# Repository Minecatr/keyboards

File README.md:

# Compiling firmware with QMK MSYS
- Install [QMK MSYS](https://msys.qmk.fm/)
- Setup QMK MSYS
- Clone this project into `qmk_firmware/keyboards/minecatr` *this means this repositories contents go in here
- Copy the build folder of the desired keyboard into the QMK MSYS directory
- Run `qmk compile -e CONVERT_TO=promicro_rp2040 -kb {PATH TO KEYBOARD} -km default` in QMK MSYS
- Output should be in `qmk_firmware/.build`
## Using other bootloaders
If your MCU does not use UF2 it likely supports one of these other bootloaders
### Caterina
`qmk flash -kb /build -km default`

### [Other Bootloaders](https://github.com/qmk/qmk_firmware/blob/master/docs/flashing.md)
# Using VIA to change layout
- Install [VIA](https://github.com/the-via/releases/releases) or use the [web version](https://www.usevia.app/)
- Navigate to settings and enable show design tab
- Navigate to design and press load
- Select the the via.json file of the desired board

a preconfigured layout.json is in each complete board

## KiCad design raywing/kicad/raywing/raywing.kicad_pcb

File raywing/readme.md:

# RAYWING

a split choc keyboard with 54 backlit keys 2 rotary encoders and a flippable board
## Parts
- RGB LEDs: SK6812 MINI-E 100pcs https://www.aliexpress.us/item/2255800289371100.html
- MCU: Any Arduino Pro Micro Form Board
- EVQWGD001 Encoder: https://www.aliexpress.us/item/3256806010310254.html
- Diodes: DO-35 1N4148 100pcs https://www.aliexpress.us/item/3256805608834808.html
- Hotswap: Mill-Max Sockets (any) https://ringerkeys.com/collections/modders-tools/products/mill-max-hot-swap-sockets?variant=32793029312594](https://mech.land/products/mill-max-sockets?variant=39832065081497
- Switches: Any Choc V1 Compatible https://chosfox.com/collections/kailh-low-profile-switch-pg1350/products/kailh-chocs
- Keycaps: Any Choc V1 Compatible
- TRRS: PJ-320A https://www.aliexpress.us/item/2251832843150354.html
- TRRS Cable: Any 4 Ring TRRS Cable
  - If you have a 3 ring cut off the last pin on the TRRS socket
## Ordering A PCB
1. Download Gerbers Located `/kicad/production/Raywing.zip`
2. Choose Preferred PCB service
  - JLCPCB: https://cart.jlcpcb.com/quote
  - PCBWAY: https://www.pcbway.com/
  - DIGIKEY: https://www.digikey.com/en/resources/design-tools/pcb-build
3. Upload Gerbers
4. Order PCB

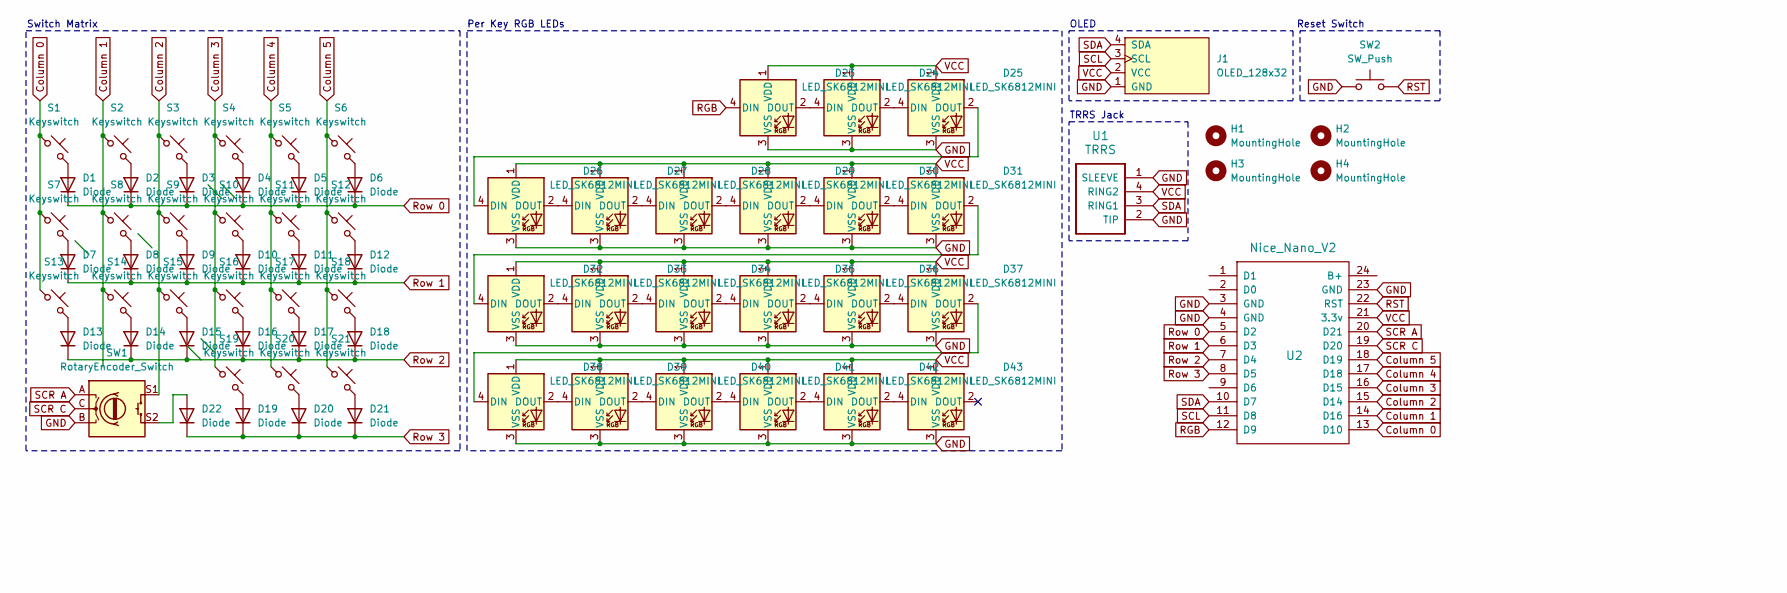
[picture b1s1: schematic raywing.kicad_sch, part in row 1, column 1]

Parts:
D1, D2, D3, D4, D5, D6, D7, D8, D9, D10, D11, D12, D13, D14, D15, D16, D17, D18, D19, D20, D21, D22: Diode; Diode_DO-35-FLIP
D23, D24, D25, D26, D27, D28, D29, D30, D31, D32, D33, D34, D35, D36, D37, D38, D39, D40, D41, D42, D43: LED_SK6812MINI; SK6812_mini_e_flipable
H1, H2, H3, H4: MountingHole; MountingHole_2.2mm_M2_Pad_Via
J1: OLED_128x32
S1, S2, S3, S4, S5, S6, S7, S8, S9, S10, S11, S12, S13, S14, S15, S16, S17, S18, S19, S20, S21: Keyswitch; Hotswap_Choc_FLIP
SW1: RotaryEncoder_Switch; evqwgd001
SW2: SW_Push; SW_SPST_TL3342_FLIP
U1: TRRS; TRRS_PJ-320A_FLIP
U2: Nice_Nano_V2

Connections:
Column 0: S1.1, S7.1, S13.1, U2.13 (D10)
Column 1: S2.1, S8.1, S14.1, U2.14 (D16)
Column 2: S3.1, S9.1, S15.1, SW1.S1, U2.15 (D14)
Column 3: S4.1, S10.1, S16.1, S19.1, U2.16 (D15)
Column 4: S5.1, S11.1, S17.1, S20.1, U2.17 (D18)
Column 5: S6.1, S12.1, S18.1, S21.1, U2.18 (D19)
GND: D23.3 (VSS), D24.3 (VSS), D25.3 (VSS), D26.3 (VSS), D27.3 (VSS), D28.3 (VSS), D29.3 (VSS), D30.3 (VSS), D31.3 (VSS), D32.3 (VSS), D33.3 (VSS), D34.3 (VSS), D35.3 (VSS), D36.3 (VSS), D37.3 (VSS), D38.3 (VSS), D39.3 (VSS), D40.3 (VSS), D41.3 (VSS), D42.3 (VSS), D43.3 (VSS), J1.1 (GND), SW1.B, SW2.1, U1.1 (SLEEVE), U1.2 (TIP), U2.3 (GND), U2.4 (GND), U2.23 (GND)
unnamed: D1.2 (A), S1.2
unnamed: D2.2 (A), S2.2
unnamed: D3.2 (A), S3.2
unnamed: D4.2 (A), S4.2
unnamed: D5.2 (A), S5.2
unnamed: D6.2 (A), S6.2
unnamed: D7.2 (A), S7.2
unnamed: D8.2 (A), S8.2
unnamed: D9.2 (A), S9.2
unnamed: D10.2 (A), S10.2
unnamed: D11.2 (A), S11.2
unnamed: D12.2 (A), S12.2
unnamed: D13.2 (A), S13.2
unnamed: D14.2 (A), S14.2
unnamed: D15.2 (A), S15.2
unnamed: D16.2 (A), S16.2
unnamed: D17.2 (A), S17.2
unnamed: D18.2 (A), S18.2
unnamed: D19.2 (A), S19.2
unnamed: D20.2 (A), S20.2
unnamed: D21.2 (A), S21.2
unnamed: D22.2 (A), SW1.S2
unnamed: D23.2 (DOUT), D24.4 (DIN)
unnamed: D24.2 (DOUT), D25.4 (DIN)
unnamed: D25.2 (DOUT), D26.4 (DIN)
unnamed: D26.2 (DOUT), D27.4 (DIN)
unnamed: D27.2 (DOUT), D28.4 (DIN)
unnamed: D28.2 (DOUT), D29.4 (DIN)
unnamed: D29.2 (DOUT), D30.4 (DIN)
unnamed: D30.2 (DOUT), D31.4 (DIN)
unnamed: D31.2 (DOUT), D32.4 (DIN)
unnamed: D32.2 (DOUT), D33.4 (DIN)
unnamed: D33.2 (DOUT), D34.4 (DIN)
unnamed: D34.2 (DOUT), D35.4 (DIN)
unnamed: D35.2 (DOUT), D36.4 (DIN)
unnamed: D36.2 (DOUT), D37.4 (DIN)
unnamed: D37.2 (DOUT), D38.4 (DIN)
unnamed: D38.2 (DOUT), D39.4 (DIN)
unnamed: D39.2 (DOUT), D40.4 (DIN)
unnamed: D40.2 (DOUT), D41.4 (DIN)
unnamed: D41.2 (DOUT), D42.4 (DIN)
unnamed: D42.2 (DOUT), D43.4 (DIN)
RGB: D23.4 (DIN), U2.12 (D9)
RST: SW2.2, U2.22 (RST)
Row 0: D1.1 (K), D2.1 (K), D3.1 (K), D4.1 (K), D5.1 (K), D6.1 (K), U2.5 (D2)
Row 1: D7.1 (K), D8.1 (K), D9.1 (K), D10.1 (K), D11.1 (K), D12.1 (K), U2.6 (D3)
Row 2: D13.1 (K), D14.1 (K), D15.1 (K), D16.1 (K), D17.1 (K), D18.1 (K), U2.7 (D4)
Row 3: D19.1 (K), D20.1 (K), D21.1 (K), D22.1 (K), U2.8 (D5)
SCL: J1.3 (SCL), U2.11 (D8)
SCR A: SW1.A, U2.20 (D21)
SCR C: SW1.C, U2.19 (D20)
SDA: J1.4 (SDA), U1.3 (RING1), U2.10 (D7)
VCC: D23.1 (VDD), D24.1 (VDD), D25.1 (VDD), D26.1 (VDD), D27.1 (VDD), D28.1 (VDD), D29.1 (VDD), D30.1 (VDD), D31.1 (VDD), D32.1 (VDD), D33.1 (VDD), D34.1 (VDD), D35.1 (VDD), D36.1 (VDD), D37.1 (VDD), D38.1 (VDD), D39.1 (VDD), D40.1 (VDD), D41.1 (VDD), D42.1 (VDD), D43.1 (VDD), J1.2 (VCC), U1.4 (RING2), U2.21 (3.3v)

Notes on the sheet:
Switch Matrix
Reset Switch
OLED
TRRS Jack
Per Key RGB LEDs

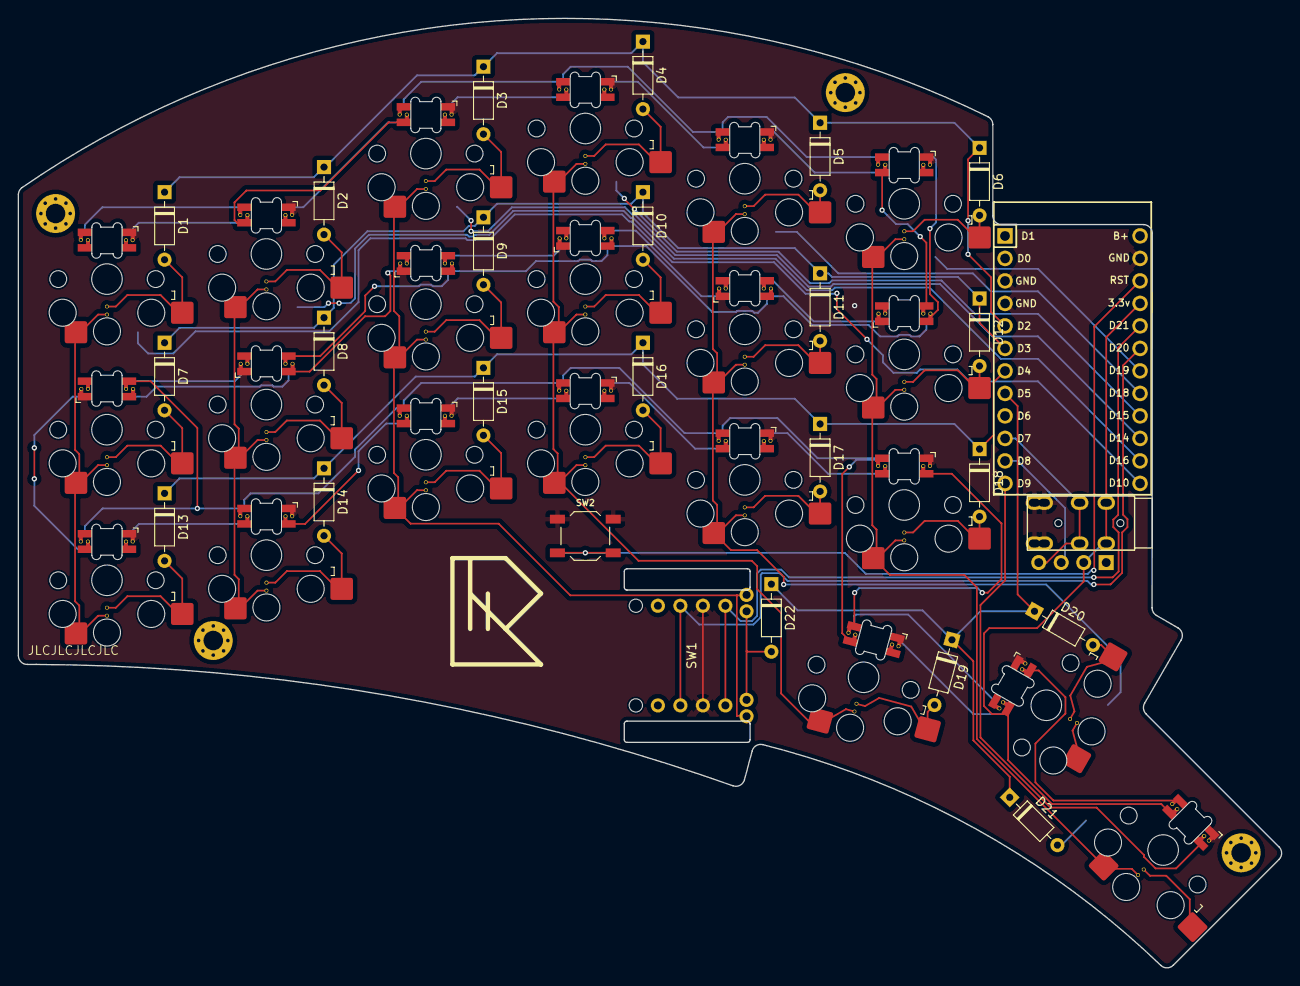
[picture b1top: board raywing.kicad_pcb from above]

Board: 2 copper layers, 142.6 x 107.2 mm, 73 parts (0 on the bottom side), 60 nets.

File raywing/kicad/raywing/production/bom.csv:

Designator,Footprint,Quantity,Value,LCSC Part #
"D1, D10, D11, D12, D13, D14, D15, D16, D17, D18, D19, D2, D20, D21, D22, D3, D4, D5, D6, D7, D8, D9",Diode_DO-35-FLIP,22,Diode,
"D23, D24, D25, D26, D27, D28, D29, D30, D31, D32, D33, D34, D35, D36, D37, D38, D39, D40, D41, D42, D43",SK6812_mini_e_flipable,21,LED_SK6812MINI,
J1,OLED_128x32,1,OLED_128x32,
"S1, S10, S11, S12, S13, S14, S15, S16, S17, S18, S19, S2, S20, S21, S3, S4, S5, S6, S7, S8, S9",Hotswap_Choc_FLIP,21,Keyswitch,
SW1,evqwgd001,1,RotaryEncoder_Switch,
SW2,SW_SPST_TL3342_FLIP,1,SW_Push,
U1,TRRS_PJ-320A_FLIP,1,TRRS,
U2,Nice_Nano_V2,1,Nice_Nano_V2,

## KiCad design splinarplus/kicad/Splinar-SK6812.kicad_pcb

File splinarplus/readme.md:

# Splinar+

(keys are scratched in btw; mbk keycaps expensive)

a split choc keyboard with 54 backlit keys 2 rotary encoders and a flippable board
## Parts
- RGB LEDs: SK6812 MINI-E 100pcs https://www.aliexpress.us/item/2255800289371100.html
- MCU: Any Arduino Pro Micro Form Board
- EVQWGD001 Encoder: https://www.aliexpress.us/item/3256806010310254.html
- Diodes: DO-35 1N4148 100pcs https://www.aliexpress.us/item/3256805608834808.html
- Hotswap: Mill-Max Sockets (any) https://ringerkeys.com/collections/modders-tools/products/mill-max-hot-swap-sockets?variant=32793029312594](https://mech.land/products/mill-max-sockets?variant=39832065081497
- Switches: Any Choc V1 Compatible https://chosfox.com/collections/kailh-low-profile-switch-pg1350/products/kailh-chocs
- Keycaps: Any Choc V1 Compatible
- TRRS: PJ-320A https://www.aliexpress.us/item/2251832843150354.html
- TRRS Cable: Any 4 Ring TRRS Cable
  - If you have a 3 ring cut off the last pin on the TRRS socket
## Ordering A PCB
1. Download Gerbers Located `/kicad/production/Splinar.zip`
2. Choose Preferred PCB service
  - JLCPCB: https://cart.jlcpcb.com/quote
  - PCBWAY: https://www.pcbway.com/
  - DIGIKEY: https://www.digikey.com/en/resources/design-tools/pcb-builde
3. Upload Gerbers
4. Order PCB

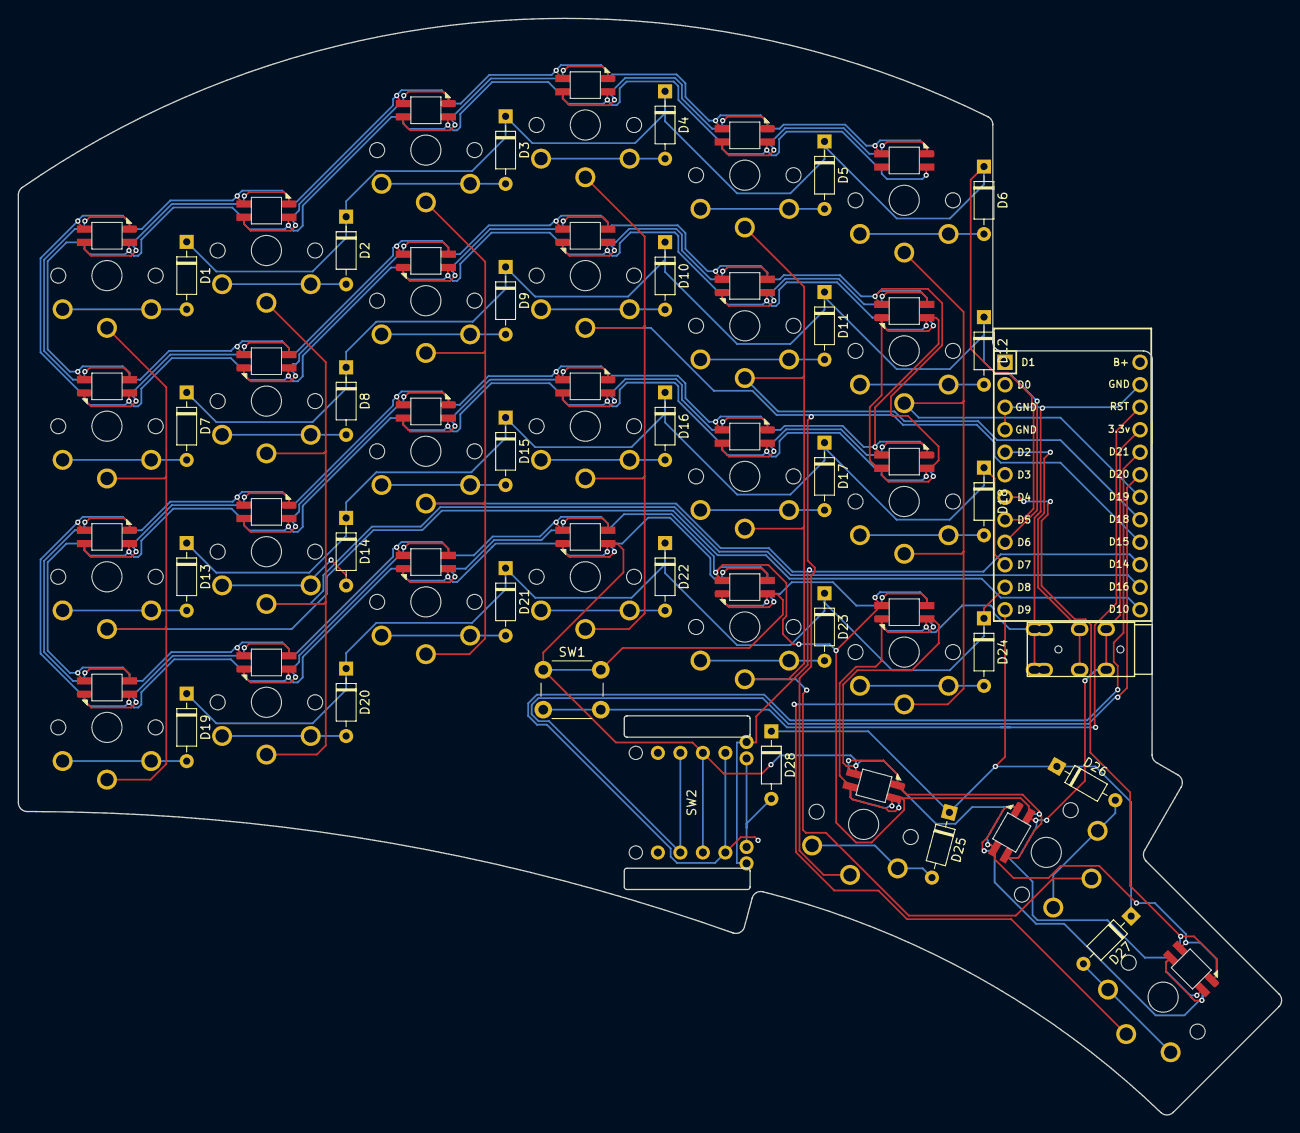
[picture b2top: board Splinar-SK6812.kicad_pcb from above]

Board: 2 copper layers, 142.6 x 123.8 mm, 86 parts (0 on the bottom side), 72 nets.

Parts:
D1, D2, D3, D4, D5, D6, D7, D8, D9, D10, D11, D12, D13, D14, D15, D16, D17, D18, D19, D20, D21, D22, D23, D24, D25, D26, D27, D28: Diode; Diode_DO-35-FLIP
D29, D30, D31, D32, D33, D34, D35, D36, D37, D38, D39, D40, D41, D42, D43, D44, D45, D46, D47, D48, D49, D50, D51, D52, D53, D54, D55: LED_SK6812MINI
S1, S2, S3, S4, S5, S6, S7, S8, S9, S10, S11, S12, S13, S14, S15, S16, S17, S18, S19, S20, S21, S22, S23, S24, S25, S26, S27: Keyswitch; Kailh-PG1350-1u-reversible-No-Clickhole
SW1: SW_Push; SW_PUSH_6mm_H4.3mm
SW2: RotaryEncoder_Switch; evqwgd001
U1: TRRS; TRRS_PJ-320A_FLIP
U2: Nice_Nano_V2

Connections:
Column 0: S1.1, S7.1, S13.1, S19.1, U2.13 (D10)
Column 1: S2.1, S8.1, S14.1, S20.1, U2.14 (D16)
Column 2: S3.1, S9.1, S15.1, S21.1, SW2.S1, U2.15 (D14)
Column 3: S4.1, S10.1, S16.1, S22.1, S25.1, U2.16 (D15)
Column 4: S5.1, S11.1, S17.1, S23.1, S26.1, U2.17 (D18)
Column 5: S6.1, S12.1, S18.1, S24.1, S27.1, U2.18 (D19)
GND: D29.2 (VSS), D30.2 (VSS), D31.2 (VSS), D32.2 (VSS), D33.2 (VSS), D34.2 (VSS), D35.2 (VSS), D36.2 (VSS), D37.2 (VSS), D38.2 (VSS), D39.2 (VSS), D40.2 (VSS), D41.2 (VSS), D42.2 (VSS), D43.2 (VSS), D44.2 (VSS), D45.2 (VSS), D46.2 (VSS), D47.2 (VSS), D48.2 (VSS), D49.2 (VSS), D50.2 (VSS), D51.2 (VSS), D52.2 (VSS), D53.2 (VSS), D54.2 (VSS), D55.2 (VSS), SW1.1, SW2.B, U1.1 (SLEEVE), U1.2 (TIP), U2.3 (GND), U2.4 (GND), U2.23 (GND)
unnamed: D1.2 (A), S1.2
unnamed: D2.2 (A), S2.2
unnamed: D3.2 (A), S3.2
unnamed: D4.2 (A), S4.2
unnamed: D5.2 (A), S5.2
unnamed: D6.2 (A), S6.2
unnamed: D7.2 (A), S7.2
unnamed: D8.2 (A), S8.2
unnamed: D9.2 (A), S9.2
unnamed: D10.2 (A), S10.2
unnamed: D11.2 (A), S11.2
unnamed: D12.2 (A), S12.2
unnamed: D13.2 (A), S13.2
unnamed: D14.2 (A), S14.2
unnamed: D15.2 (A), S15.2
unnamed: D16.2 (A), S16.2
unnamed: D17.2 (A), S17.2
unnamed: D18.2 (A), S18.2
unnamed: D19.2 (A), S19.2
unnamed: D20.2 (A), S20.2
unnamed: D21.2 (A), S21.2
unnamed: D22.2 (A), S22.2
unnamed: D23.2 (A), S23.2
unnamed: D24.2 (A), S24.2
unnamed: D25.2 (A), S25.2
unnamed: D26.2 (A), S26.2
unnamed: D27.2 (A), S27.2
unnamed: D28.2 (A), SW2.S2
unnamed: D29.3 (DIN), D55.1 (DOUT)
unnamed: D30.1 (DOUT), D31.3 (DIN)
unnamed: D31.1 (DOUT), D32.3 (DIN)
unnamed: D32.1 (DOUT), D33.3 (DIN)
unnamed: D33.1 (DOUT), D34.3 (DIN)
unnamed: D34.1 (DOUT), D35.3 (DIN)
unnamed: D35.1 (DOUT), D36.3 (DIN)
unnamed: D36.1 (DOUT), D37.3 (DIN)
unnamed: D37.1 (DOUT), D38.3 (DIN)
unnamed: D38.1 (DOUT), D39.3 (DIN)
unnamed: D39.1 (DOUT), D40.3 (DIN)
unnamed: D40.1 (DOUT), D41.3 (DIN)
unnamed: D41.1 (DOUT), D42.3 (DIN)
unnamed: D42.1 (DOUT), D43.3 (DIN)
unnamed: D43.1 (DOUT), D44.3 (DIN)
unnamed: D44.1 (DOUT), D45.3 (DIN)
unnamed: D45.1 (DOUT), D46.3 (DIN)
unnamed: D46.1 (DOUT), D47.3 (DIN)
unnamed: D47.1 (DOUT), D48.3 (DIN)
unnamed: D48.1 (DOUT), D49.3 (DIN)
unnamed: D49.1 (DOUT), D50.3 (DIN)
unnamed: D50.1 (DOUT), D51.3 (DIN)
unnamed: D51.1 (DOUT), D52.3 (DIN)
unnamed: D52.1 (DOUT), D53.3 (DIN)
unnamed: D53.1 (DOUT), D54.3 (DIN)
unnamed: D54.1 (DOUT), D55.3 (DIN)
RGB: D30.3 (DIN), U2.7 (D4)
RST: SW1.2, U2.22 (RST)
Row 0: D1.1 (K), D2.1 (K), D3.1 (K), D4.1 (K), D5.1 (K), D6.1 (K), U2.8 (D5)
Row 1: D7.1 (K), D8.1 (K), D9.1 (K), D10.1 (K), D11.1 (K), D12.1 (K), U2.9 (D6)
Row 2: D13.1 (K), D14.1 (K), D15.1 (K), D16.1 (K), D17.1 (K), D18.1 (K), U2.10 (D7)
Row 3: D19.1 (K), D20.1 (K), D21.1 (K), D22.1 (K), D23.1 (K), D24.1 (K), U2.11 (D8)
Row 4: D25.1 (K), D26.1 (K), D27.1 (K), D28.1 (K), U2.12 (D9)
SCR A: SW2.A, U2.20 (D21)
SCR C: SW2.C, U2.19 (D20)
SDA: U1.3 (RING1), U2.5 (D2)
VCC: D29.4 (VDD), D30.4 (VDD), D31.4 (VDD), D32.4 (VDD), D33.4 (VDD), D34.4 (VDD), D35.4 (VDD), D36.4 (VDD), D37.4 (VDD), D38.4 (VDD), D39.4 (VDD), D40.4 (VDD), D41.4 (VDD), D42.4 (VDD), D43.4 (VDD), D44.4 (VDD), D45.4 (VDD), D46.4 (VDD), D47.4 (VDD), D48.4 (VDD), D49.4 (VDD), D50.4 (VDD), D51.4 (VDD), D52.4 (VDD), D53.4 (VDD), D54.4 (VDD), D55.4 (VDD), U1.4 (RING2), U2.21 (3.3v)

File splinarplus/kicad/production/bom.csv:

Designator,Footprint,Quantity,Value,LCSC Part #
"D1, D10, D11, D12, D13, D14, D15, D16, D17, D18, D19, D2, D20, D21, D22, D23, D24, D25, D26, D27, D28, D3, D4, D5, D6, D7, D8, D9",Diode_DO-35-FLIP,28,Diode,
"D29, D30, D31, D32, D33, D34, D35, D36, D37, D38, D39, D40, D41, D42, D43, D44, D45, D46, D47, D48, D49, D50, D51, D52, D53, D54, D55",SK6812_mini_e_flipable,27,LED_SK6812MINI,
"S1, S10, S11, S12, S13, S14, S15, S16, S17, S18, S19, S2, S20, S21, S22, S23, S24, S25, S26, S27, S3, S4, S5, S6, S7, S8, S9",Kailh-PG1350-1u-reversible-No-Clickhole,27,Keyswitch,
SW1,SW_PUSH_6mm_H4.3mm,1,SW_Push,
SW2,evqwgd001,1,RotaryEncoder_Switch,
U1,TRRS_PJ-320A_FLIP,1,TRRS,
U2,Nice_Nano_V2,1,Nice_Nano_V2,

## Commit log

2024-04-06 upload
2024-04-06 change splinar2 to splinar+
2024-05-26 test
2024-05-27 Add rgb matrix
2024-05-28 fix switch
2025-02-26 raywing finished
